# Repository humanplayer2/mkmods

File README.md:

# Mechanical Keyboard Mods
 
Notes and photos of some of the boards and techniques I've fiddled with.  
> [3D Printing](#3d-printing) | [Building Techniques](#building-techniques) | [Ergogen](#ergogen) | [Mods](#mods) | [Misc](#misc)  
> [Homemade Boards](#homemade-boards) | [Premade Boards](#premade-boards) | [Reviews](#reviews)  

## Homemade Boards
- [Underset: A spartan 52-key column-staggered split keyboard](homemade/underset/README.md)  
    The aggressive pinky stagger of LaserRaven with numbers row and RP2040-Zero and TRRS underset the switch plate for simple cases that still isolates the electronics  
       
        - [Now also in a v2 with USB-C instead of TRRS](https://codeberg.org/humanplayer2/underset)  
- [LaserRaven: A 32+6 designed with nordic languages in mind.](homemade/laserraven/README.md)  
    My daily board (left), a sligthy hacked version of the v1 PCB (right)  
       
- [LaserProsthetic: Trackpoint ergo laser-cut from acrylic and MDF](homemade/laserprosthetic/README.md)  
    Precursor to LaserRaven, laser-cut from acrylic and MDF.  
       
- [Frejas Hitbox: A gamepad made of Hama beads and cardboard](homemade/frejas/README.md)  
    Made for and with my toddler.  
     
- [Lite-Puter Footpanel: Light-controller rewired to run QMK](homemade/liteputer/README.md)  
    A friend wanted foot-modifiers, so we wired this light controller to a QMK MCU.  
     
- [Scraps34: A split build on a sawn TKL plate](homemade/scraps34/README.md)  
    When you've definitively destroyed the main chip on the PCB.  

## 3D Printing
- [1x1 MX plate test print](3dprint/1x1_mx_plate/README.md)
- [Silakka54 cases](3dprint/silakka54/README.md)
- [ThinkPad keycap MX stems](3dprint/thinkpad_mx_stems/README.md)
- [Comparision of JLC3DP SLA materials for keycaps (sponsored)](3dprint/jlc3dp_sla_keycaps/README.md)

## Building Techniques
- [Solder-free handwiring using WireGlue: Tests](techniques/wireglue/README.md)
- [Insulating handwired builds easily with acrylic paint](techniques/acrylic_paint_as_insulator/README.md)
- [A plate made of Hama beads](techniques/hama_plate/README.md)

## Ergogen
- [Script for running `ergogen .` on any `filename.yaml`](ergogen/ergogendot_on_any_filename)
- [My custom Ergogen footprints](https://codeberg.org/humanplayer2/ergogen_footprints)

## Mods
- [Spacebar with adhesive putty for deeper sound](mods/spacebar_with_adhesive_putty/README.md)
- [Hotswap mod using cheap rivets](mods/rivet_hotswap/README.md)
- [Heat shrink on stablizers to reduce rattle (didn't work)](mods/heat_shrink_on_stablizers/README.md)

## Misc
- [Gabrielle 7007L typewriter: MX useable keycaps](misc/Gabriel_7007L/README.md)
- [Retro-bright keycaps in the oven](misc/retrobright/README.md)

## Premade Boards
- [Tokyo60 w. Terminal keycaps: Notes on QMK/VIA](premade/Tokyo60/README.md)
- [ZUOYA GMK26: Teardown, VIA instructions](premade/Zuoya_GMK26/README.md)
- [ZUOYA GMK87: Notes on firmware and VIA]([premade/Zuoya_GMK87/README.md)
- [WIP: TEX Shura w. modified Cherry profile keycaps](premade/TEX_Shura/README.md)

## Reviews
- [Ordering PCBs from PCBWay: How-to and review (sponsored)](reviews/PCBWay/pcbway_review.md)
- [AKKO 3068B with DK keycaps (sponsored)](reviews/AKKO_3068B/README.md)
- [Dareu Cool 60 (sponsored)](reviews/Darea_Cool60/README.md)
- [MUCAI MK61: 10$ complete hotswap 60% board](reviews/MUCAI_MK61/README.md)

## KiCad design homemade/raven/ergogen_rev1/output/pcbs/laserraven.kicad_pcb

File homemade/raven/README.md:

# Raven38

> **A 32+6 trackpoint columnar aggressive stagger unibody split
with horizontal little finger cluster and fourth leech finger key designed with nordic languages in mind.**

- Designed with [Ergogen](https://github.com/ergogen/ergogen)
- [My QMK fork](https://github.com/humanplayer2/qmk_firmware) contains firmware, in the `humanplayer2` branch, under `keyboards/humanplayer2/raven/`.

*Revision 1 (wip). Pinkie fans moved inwards, no splay*

*Version 1: Far, splayed pinky fans*

*Next steps:*
- V2: Ergogen+KiCad a PCB, design case.
- Document change from V1 to Rev. 1.
- V1: Add note that outlines needed to be closed manually in KiCad.

# Build Rationale and Notes

- Ravens are black, like ThinkPads, that have trackpoints.
- Ravens are smart tool users. They should love lasers---and trackpoints.
- Lasers are hot. I thought I'd laser cut the case. Now I have a 3D printer...

## Trackpoint
I really like ThinkPads (X301, you hold my heart). Not least for their trackpoints. I love trackpoints. For my day-to-day computing, I need no other pointing device.

## 32 alpha keys
As a Dane writing frequent Danish and English, on my main layer, I want a 29 letter alphabet (ABC...WXYZ+ÆØÅ). I also want dot and comma. That's 31 keys. For symmetry, that makes 32 keys. Tab, you're in.

## Little finger fans / horizontal pinky clusters
I like a somewhat aggresive pinky stagger of 1u. I don't find it nice to reach further down than that, so I have no pinky keys under the home row.

Reaching straight up with my pinky is not something I enjoy. On my [Laser Prosthetic](../LaserProsthetic/README.md), I have pinky clusters where I reach up and out a bit. That's fine, but requires a bit of a hand lift.

With the outer-most key on this board, I'm experimenting with how it'll feel to reach only outwards. The pinky fan has a radius the length of my pinky.

## Outer ring
With 6 index, 3 middle, 3 ring, and 3 pinky keys, I need two extra keys somewhere to reach 32.

I could add them on the far inside, and reach in with my left index. I have tried those on my Laser Prothetic.

Instead, I've taken a page from the book of my 100 US wpm collegue, who types without pinkies. They use the ring fingers for those pinky keys instead. Given the 1u staggered pinky fans, there's ample space for an outer ring finger key.

*KLE sketch of keys for DK Qwerty. Dash (-) marks home row keys.*

## Thumb keys, mouse buttons and layers
I've added 6 thumb keys because this is the maximum amount I find nice to reach.

Two thumb keys are for the trackpoint: One for left click (and dragging), one middle click (and scrolling). Right click is Shift + middle click.

I use six layers: Shift, Ctrl, Alt, Navigation, Numbers and Symbols. Four are on thumb keys, while the two least used are on pinkies (Alt and Numbers).

## Ergogen & KiCad
I have followed . I use  through the command line, on Fedora. Install by `sudo npm -g i ergogen`. From the board's `ergogen` directory, run `ergogen config.yaml`. From there, traces have to be drawn manually in Kicad.

I followed  to add a graphics silkscreen in KiCad.

I forgot to include my Ergogen screw holes before routing. I imported the Ergogen-generated outline of them, positioned them manually referring to an untraced copy that included them, and added them to the Edge.Cuts layer.

## Competents

### PCB
 I made a quick comparison of JLCPCB and PCBWay, and the former gave me a far lower rate. I ordered the minimum of 5 PCBs, FR-4, 1.6mm, LeadFree HASL.
 - `36.83 Euro`  with the cheapest 10-14 days shipping, taxes, and a new customer coupon.

### Trackpoint and controller
[Holykeebs Trackpoint module](https://docs.holykeebs.com/guides/trackpoint-module/) kit, incl. black opaque shield, custom low headers and 
    - `112 USD` for 2, free shipping, taxes not included.

### Soldered components
- 38 Kaihl hotswap sockets. `3.62 USD` for 40.
- W1 1N4148 SOD-123 diodes, 38 pieces. `2.53 USD` for 100.
- 10x short profile header sockets (2.54mm, Ph3.5, female headers 12P), as I messed one up: `7.86 USD`.

### Case and Plate
- I had planned to laser-cut a case, but now I bought a 3D printer... TODO.

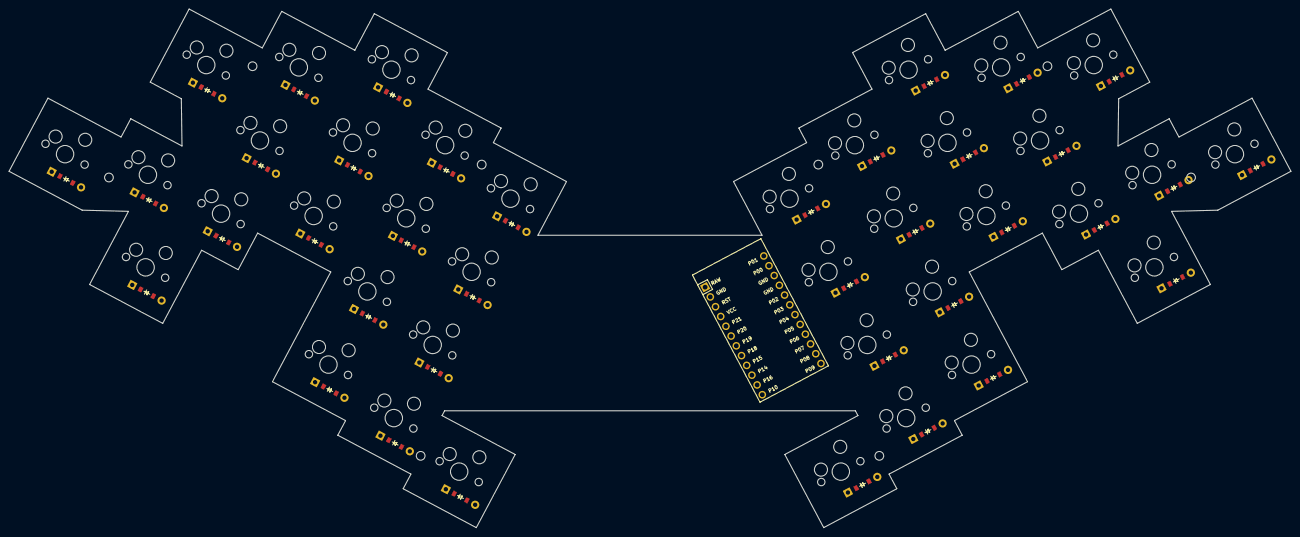
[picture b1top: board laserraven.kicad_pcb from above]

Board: 2 copper layers, 294.0 x 118.9 mm, 77 parts (0 on the bottom side), 52 nets, no tracks yet.

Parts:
D1, D2, D3, D4, D5, D6, D7, D8, D9, D10, D11, D12, D13, D14, D15, D16, D17, D18, D19, D20, D21, D22, D23, D24, D25, D26, D27, D28, D29, D30, D31, D32, D33, D34, D35, D36, D37, D38: ComboDiode
MCU1: ProMicro
S1, S2, S3, S4, S5, S6, S7, S8, S9, S10, S11, S12, S13, S14, S15, S16, S17, S18, S19, S20, S21, S22, S23, S24, S25, S26, S27, S28, S29, S30, S31, S32, S33, S34, S35, S36, S37, S38: MX

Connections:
GND: MCU1.2, MCU1.15, MCU1.16
P0: MCU1.14, S13.1, S14.1, S15.1, S19.1, S32.1, S33.1, S34.1, S38.1
P1: MCU1.13, S10.1, S11.1, S12.1, S18.1, S29.1, S30.1, S31.1, S37.1
P6: D25.1, D28.1, D31.1, D34.1, D35.1, MCU1.21
P7: D22.1, D24.1, D27.1, D30.1, D33.1, MCU1.22
P8: D21.1, D23.1, D26.1, D29.1, D32.1, MCU1.23
P9: D20.1, D36.1, D37.1, D38.1, MCU1.24
P10: D1.1, D17.1, D18.1, D19.1, MCU1.12
P14: D3.1, D5.1, D8.1, D11.1, D14.1, MCU1.10
P15: D6.1, D9.1, D12.1, D15.1, D16.1, MCU1.9
P16: D2.1, D4.1, D7.1, D10.1, D13.1, MCU1.11
P19: MCU1.7, S7.1, S8.1, S9.1, S17.1, S26.1, S27.1, S28.1, S36.1
P20: MCU1.6, S1.1, S2.1, S3.1, S16.1, S20.1, S21.1, S22.1, S35.1
P21: MCU1.5, S4.1, S5.1, S6.1, S23.1, S24.1, S25.1
far_home: D1.2, S1.2
home_thumb: D18.2, S18.2
in_thumb: D19.2, S19.2
index_bottom: D10.2, S10.2
index_home: D11.2, S11.2
index_top: D12.2, S12.2
inner_bottom: D13.2, S13.2
inner_home: D14.2, S14.2
inner_top: D15.2, S15.2
mid_home: D2.2, S2.2
middle_bottom: D7.2, S7.2
middle_home: D8.2, S8.2
middle_top: D9.2, S9.2
mirror_far_home: D20.2, S20.2
mirror_home_thumb: D37.2, S37.2
mirror_in_thumb: D38.2, S38.2
mirror_index_bottom: D29.2, S29.2
mirror_index_home: D30.2, S30.2
mirror_index_top: D31.2, S31.2
mirror_inner_bottom: D32.2, S32.2
mirror_inner_home: D33.2, S33.2
mirror_inner_top: D34.2, S34.2
mirror_mid_home: D21.2, S21.2
mirror_middle_bottom: D26.2, S26.2
mirror_middle_home: D27.2, S27.2
mirror_middle_top: D28.2, S28.2
mirror_out_thumb: D36.2, S36.2
mirror_pinky_home: D22.2, S22.2
mirror_ring_bottom: D23.2, S23.2
mirror_ring_home: D24.2, S24.2
mirror_ring_midtop: D35.2, S35.2
mirror_ring_top: D25.2, S25.2
out_thumb: D17.2, S17.2
pinky_home: D3.2, S3.2
ring_bottom: D4.2, S4.2
ring_home: D5.2, S5.2
ring_midtop: D16.2, S16.2
ring_top: D6.2, S6.2

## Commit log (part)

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2023-06-08 AnnePro2 image test
2023-06-08 image test
2023-06-08 AnnePro2 rivet description
2023-06-08 AnnePro2 readme typesetting
2023-06-08 AnnePro2 typesetting
2023-06-08 README TOC and AnnePro2 hotswap complete
2023-06-08 AnnePro2: Typos and grammar
2023-06-09 Note to not use too much solder on rivets.
2023-08-26 add rivets image
2023-08-26 ali_rivets: png not jpg
2023-09-28 Laser Prosthetic
2023-09-28 Update README.md
    URL typo
2023-09-28 Photo path fix
2023-09-28 Photo URL fix again...
2023-12-03 Laser Prothetic QMK
2023-12-08 wip to solve that Shift is annoying on rolls
2024-01-22 LitePuter
2024-02-07 Focus revisions. 4 is most versatile, but requires GNOME changes, main Window Action to e.g. Alt, plus WSMatrix non-0 timeout, both as spaces now activate layers instead of acting as custom GUI keys.
2024-02-21 focus4 update
2024-02-21 focus4: restore LGUI open and close tab
2024-02-22 curly brackets på LGUI
2024-03-01 focus5 update: top row replacements
2024-03-11 Tab and At on ENTER_MOD
2024-03-14 Frejas Hitbox write-up
2024-03-14 Frejas Hitbox, add to README TOC, add QMK
2024-03-21 add compose key
2024-04-05 scraps34 qmk
2024-04-05 tokyo60 rename -- does README.md show?
2024-04-05 qmk directory rename
2024-04-05 tokyo60: add photos and build info
2024-04-05 .md renaming so shown when entering directory
2024-04-05 tokyo60 add photo of kit just because
2024-04-05 README formatting
2024-04-05 scraps34 init readme
2024-04-05 focus6: more on left, base f1-12, copy/paste by Ins
2024-04-05 more descriptive subtitle
2024-04-06 Update README.md
    Image extension fix
2024-04-06 volume on base
2024-04-06 added é on base, S(é) is faulty: È
2024-04-07 liteputer build log and photos
2024-05-28 ø on left side, z hard to reach, plus minor specials
2024-06-20 no space on right side
2024-06-23 Scrap forked readme
2024-06-26 focus7: Shift on rigth thumb, Ctl on index fingers
2024-07-01 for paperwm
2024-07-01 Fedora comments
2024-07-02 fedora readme notes
2024-07-28 Feature test: Quick thumb1 to thumb2 slide activates both
2024-07-28 PaperWM on Fedora keymap
2024-08-01 version and ids
2024-08-01 clean-up and thumb keys
2024-10-08 initial
2024-10-08 image path
2024-10-08 corrections
2024-10-08 addition about firmware
2024-10-08 conclusion additions
2024-10-08 typos
2024-10-09 morning after revisions
2024-10-11 rename dir
2024-10-11 post-reddit edits
2024-10-15 fedora qmk to laser readme
2024-10-15 last Forge keymap
2024-10-15 scrolling tiling keymap init
2024-10-15 Scraps34 init
2024-10-15 Fedora 40 udev rule fix
2024-10-15 PaperWM keymaps renamed
2024-10-15 Karousel keymap init
2024-10-21 prettify keymap
2024-10-22 rm old keymaps
2024-10-22 Revert "rm old keymaps"
    This reverts commit e04a0cb4374c160b4d6af16731883d4183c3ecb8.
2024-10-22 rm laser keymaps for old json
2024-10-22 Laser: Clean info.json, upd keymap, mv old keymaps to branch (#1)
    - Clean info.json so only positions that exist in the physical matrix are represented.
    - Update current keymap to fit new json.
    - Move old keymaps to own branch: laser_unused_stuff.
2024-10-25 zuoya-gmk26 initial
2024-10-25 images in readme
2024-10-25 info on mods
2024-10-28 Mention passing "QMK test": LT(1,KC_BSPC)
2024-10-28 Rephrasing
2024-11-07 init
2024-11-22 add ZUOYA org json, comment on own messed up json
2024-12-21 Last Sync: 2024-12-21 14:30:32 (Mobile)
2024-12-21 Last Sync: 2024-12-21 14:53:59 (Mobile)
2024-12-26 Comment on Scraps34 photos
2024-12-27 Some details on asymmetry, extra switches holes
2024-12-27 Mention controller type
2025-01-07 repo restructure
2025-01-07 links fix
2025-01-07 image link test
2025-01-07 non-wiki links for images
2025-01-07 Expand TOC
2025-01-07 abm066 readme
2025-01-07 image paths consistency
2025-01-07 qmk source from Zuoya, comments on futility
2025-01-07 typo
2025-01-09 ignore .exe
2025-01-09 README update, WIP
2025-01-09 image path and selection
2025-01-09 GitSync test
2025-01-09 GitSync test 2
2025-01-09 name choice and design notes
2025-01-09 ignore *.wip
2025-01-09 order
2025-01-09 GitSync deletion test
2025-01-09 reformulation
2025-01-13 details
2025-01-13 grammar and switch note
2025-01-14 GitSync pull test
2025-01-14 GitSync conflict.
2025-01-14 GitSync manual conflict
2025-01-14 GitSync conflict test
2025-01-14 GitSync manual pull testing
2025-01-14 remove GitSync test lines
2025-01-14 GitSync test, Github commit
2025-01-14 Manual sync commit
2025-01-14 GitSync pull test: conflict
2025-01-14 ergogen incl. outline, pcb, nets
2025-01-14 rm GitSync test comment
2025-01-14 rm old ergogen file
2025-01-14 gitui fix test
2025-01-14 gitui test success
2025-01-15 meta: author and version
2025-01-15 1,5 mm acrylic is hard to find
2025-01-15 SeaPicro pinout
2025-01-16 tighten thumb cluster
2025-01-16 tighter pcb, split plates, screw holes, case wip
2025-01-16 some change
2025-01-20 ordered pcb
2025-01-20 kicad 3d
2025-01-21 Solder components, rephrasings
2025-01-21 unknown change
2025-01-21 rm GitSync conflict test line
2025-01-22 TEX Shura init
2025-01-24 #small test
2025-02-13 rm wip, ergogen outputs.
2025-02-13 todo items
2025-02-14 README
2025-02-17 clean up
2025-02-17 decapitalize
2025-02-19 decapitalize dirs, mv firmware to qmk fork, updater readmes
2025-02-23 header sockets
2025-02-26 internal link fixes
2025-02-26 add photo
2025-03-01 Packaging photo
2025-03-01 Wire Glue text
2025-03-01 dir rename
2025-03-01 rephrasings
2025-03-02 cleaning test and typesetting
2025-03-02 typesetting
2025-03-15 hama plate init
2025-04-14 Typo to minor rephrasing.
2025-04-22 ergogen notes
2025-04-22 plate hole size note
2025-04-22 plate cuts
2025-04-22 darker bunnies
2025-04-27 inwards pinky fan version
2025-04-27 init ergogen wip
2025-04-27 1x1 plate
2025-04-27 produced pcb
2025-04-30 rev1 initial mention
2025-04-30 rename to version
2025-04-30 add laserraven rev1 image
2025-05-02 less init
2025-05-02 motivation, rename dir
2025-05-02 readme, rename dir
2025-05-02 Hama writes "Hama" not HAMA
2025-05-02 add wireglue
2025-05-02 less is more
2025-05-02 add text, links to resources
2025-05-02 no more laser
2025-05-23 the laser stays
2025-06-08 less
2025-06-11 Update ZUOYA GMK26 configuration with new firmware json
2025-06-13 Update ZUOYA GMK26 configuration with new firmware json (#7)
2025-07-24 grammar
2025-09-14 3d print init
2025-09-14 write-up init
2025-09-14 files and printing comments
2025-09-14 ThinkPad MX stems
2025-09-14 add FRU
2025-09-15 sacrilege
2025-10-08 add version info
2025-10-25 v13 only
2025-10-25 finish readme
2025-10-25 Sildetønde (#9)
2025-10-25 toc and printables link
2025-11-05 redo onshape links
2025-11-13 v1.2 case
2025-11-13 caution update
2025-11-13 Case for Silakka54 v1.2 (#10)
    * v1.2 case
    * typesetting
    * caution update
2025-11-13 silakka link fix
2025-11-19 unedited write-up
2025-11-19 edit text, add images
2025-11-19 dareu review
2025-11-23 jlc3dp write-up
2025-11-24 day1
2025-11-24 photo comments
2025-11-25 SLA print material comparison (#11)
2025-12-04 add some post links
2025-12-04 rm never-to-be case stumps
2026-01-27 `ergogen .` on any filename
2026-01-27 oven retro-bright
2026-01-27 10 hours
2026-01-27 Oven retro-bright (#12)
2026-01-30 v1.1
2026-02-03 placeholder
2026-02-04 pcbway review
2026-03-06 underset
2026-03-06 linebreak
2026-03-06 Underset (#13)
2026-03-06 TOC consistency
2026-04-23 link fix
2026-04-23 move reviews to dedicated directory
2026-04-23 move reviews to dedicated directory (#14)
2026-04-24 strikethrough?
2026-04-24 strikethrough paragraph
2026-04-24 Creditcards added (#15)
2026-05-05 Payment options (#17)
2026-05-07 better chip identification shots
